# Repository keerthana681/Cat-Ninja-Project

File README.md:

# Cat Ninja Handheld Console Game
 
A handheld gaming console built from scratch for UT Austin's ECE319H (Introduction to Embedded Systems), featuring a custom PCB, dual-LCD displays, and an interrupt-driven game engine.
 
## Overview
 
Cat Ninja is a fully custom embedded gaming handheld built around the TI MSPM0 microcontroller. The project spans the full hardware-software stack: a custom-designed PCB, analog input sampling via joystick and slide potentiometer, a discrete DAC for in-game sound, and a real-time game engine driven by hardware timers and interrupts.
 
## Features
 
- **Custom PCB** designed in KiCad, integrating the TI MSPM0 microcontroller with dual-LCD displays and a joystick interface
- **Dual-LCD setup** — one screen renders the live game, the other displays the score and a reactive cat sprite (happy when fish are sliced, sad when a bomb is hit or a life is lost)
- **Original hand-drawn sprite art** for the cat cursor, fish, sliced-fish states, and bombs
- **Analog input sampling** via ADC for the joystick (menu navigation and cursor movement) and slide potentiometer (in-game volume control)
- **5-bit binary-weighted DAC** for real-time sound effects (slicing, explosions, and more)
- **Interrupt-driven game engine** written in C++, using SysTick and TimerG12 for periodic game logic, rendering, and input polling
- **Finite state machine (FSM) architecture** driving the title menu, settings, gameplay, pause, and game-over screens
## How to Play
 
**Menu Navigation**
- On the title screen, move the joystick to switch between **Info**, **Settings**, and **Play**
- One button **selects** the highlighted option; the other button **goes back** to the previous screen
- **Info** explains how to play
- **Settings** lets you change the display language (English/Spanish)
**Gameplay**
- Move the cat paw cursor around the screen using the joystick
- Press the select button to **slice** — this triggers a slicing sound and swaps the fish sprite to its sliced state
- Fish rise and fall across the screen at random; slice them to score points
- Bombs appear at random alongside the fish — avoid slicing these
- You have **3 lives**. You lose a life if you let a fish fall unsliced, or if you slice a bomb (which also triggers an explosion sound)
- When you run out of lives, the game ends with a crying-cat sound effect
- The volume of in-game sound effects is controlled in real time by the slide potentiometer
## Hardware
 
- TI MSPM0 microcontroller
- Dual-LCD display setup
- Joystick + slide potentiometer analog inputs
- Custom binary-weighted DAC circuit for audio output
- PCB designed and fabricated for this project (see `/hardware` for KiCad files and schematics)
## Software
 
- Core game engine written in C++
- SysTick and TimerG12 used for periodic, interrupt-driven task scheduling
- ADC driver for analog input sampling
- DAC output driver for sound playback
## Team
 
Built by Keerthana Mangalpally and Kaitlyn Chen for ECE319H at UT Austin.
 
## Acknowledgments & License
 
This project uses hardware driver code adapted from course materials provided by Dr. Jonathan Valvano for UT Austin's embedded systems curriculum, used under the license below.
 
```
Simplified BSD License (FreeBSD License)
Copyright © 2025, Jonathan Valvano, All rights reserved.
 
Redistribution and use in source and binary forms, with or without modification,
are permitted provided that the following conditions are met:
 
1. Redistributions of source code must retain the above copyright notice,
   this list of conditions and the following disclaimer.
2. Redistributions in binary form must reproduce the above copyright notice,
   this list of conditions and the following disclaimer in the documentation
   and/or other materials provided with the distribution.
 
THIS SOFTWARE IS PROVIDED BY THE COPYRIGHT HOLDERS AND CONTRIBUTORS "AS IS"
AND ANY EXPRESS OR IMPLIED WARRANTIES, INCLUDING, BUT NOT LIMITED TO, THE
IMPLIED WARRANTIES OF MERCHANTABILITY AND FITNESS FOR A PARTICULAR PURPOSE
ARE DISCLAIMED. IN NO EVENT SHALL THE COPYRIGHT OWNER OR CONTRIBUTORS BE
LIABLE FOR ANY DIRECT, INDIRECT, INCIDENTAL, SPECIAL, EXEMPLARY, OR CONSEQUENTIAL
DAMAGES (INCLUDING, BUT NOT LIMITED TO, PROCUREMENT OF SUBSTITUTE GOODS OR SERVICES;
LOSS OF USE, DATA, OR PROFITS; OR BUSINESS INTERRUPTION) HOWEVER CAUSED
AND ON ANY THEORY OF LIABILITY, WHETHER IN CONTRACT, STRICT LIABILITY,
OR TORT (INCLUDING NEGLIGENCE OR OTHERWISE) ARISING IN ANY WAY OUT OF THE
USE OF THIS SOFTWARE, EVEN IF ADVISED OF THE POSSIBILITY OF SUCH DAMAGE.
 
The views and conclusions contained in the software and documentation are
those of the authors and should not be interpreted as representing official
policies, either expressed or implied, of the FreeBSD Project.
```
 
For more information on the original course materials, see [Dr. Valvano's course page](http://users.ece.utexas.edu/~valvano/).

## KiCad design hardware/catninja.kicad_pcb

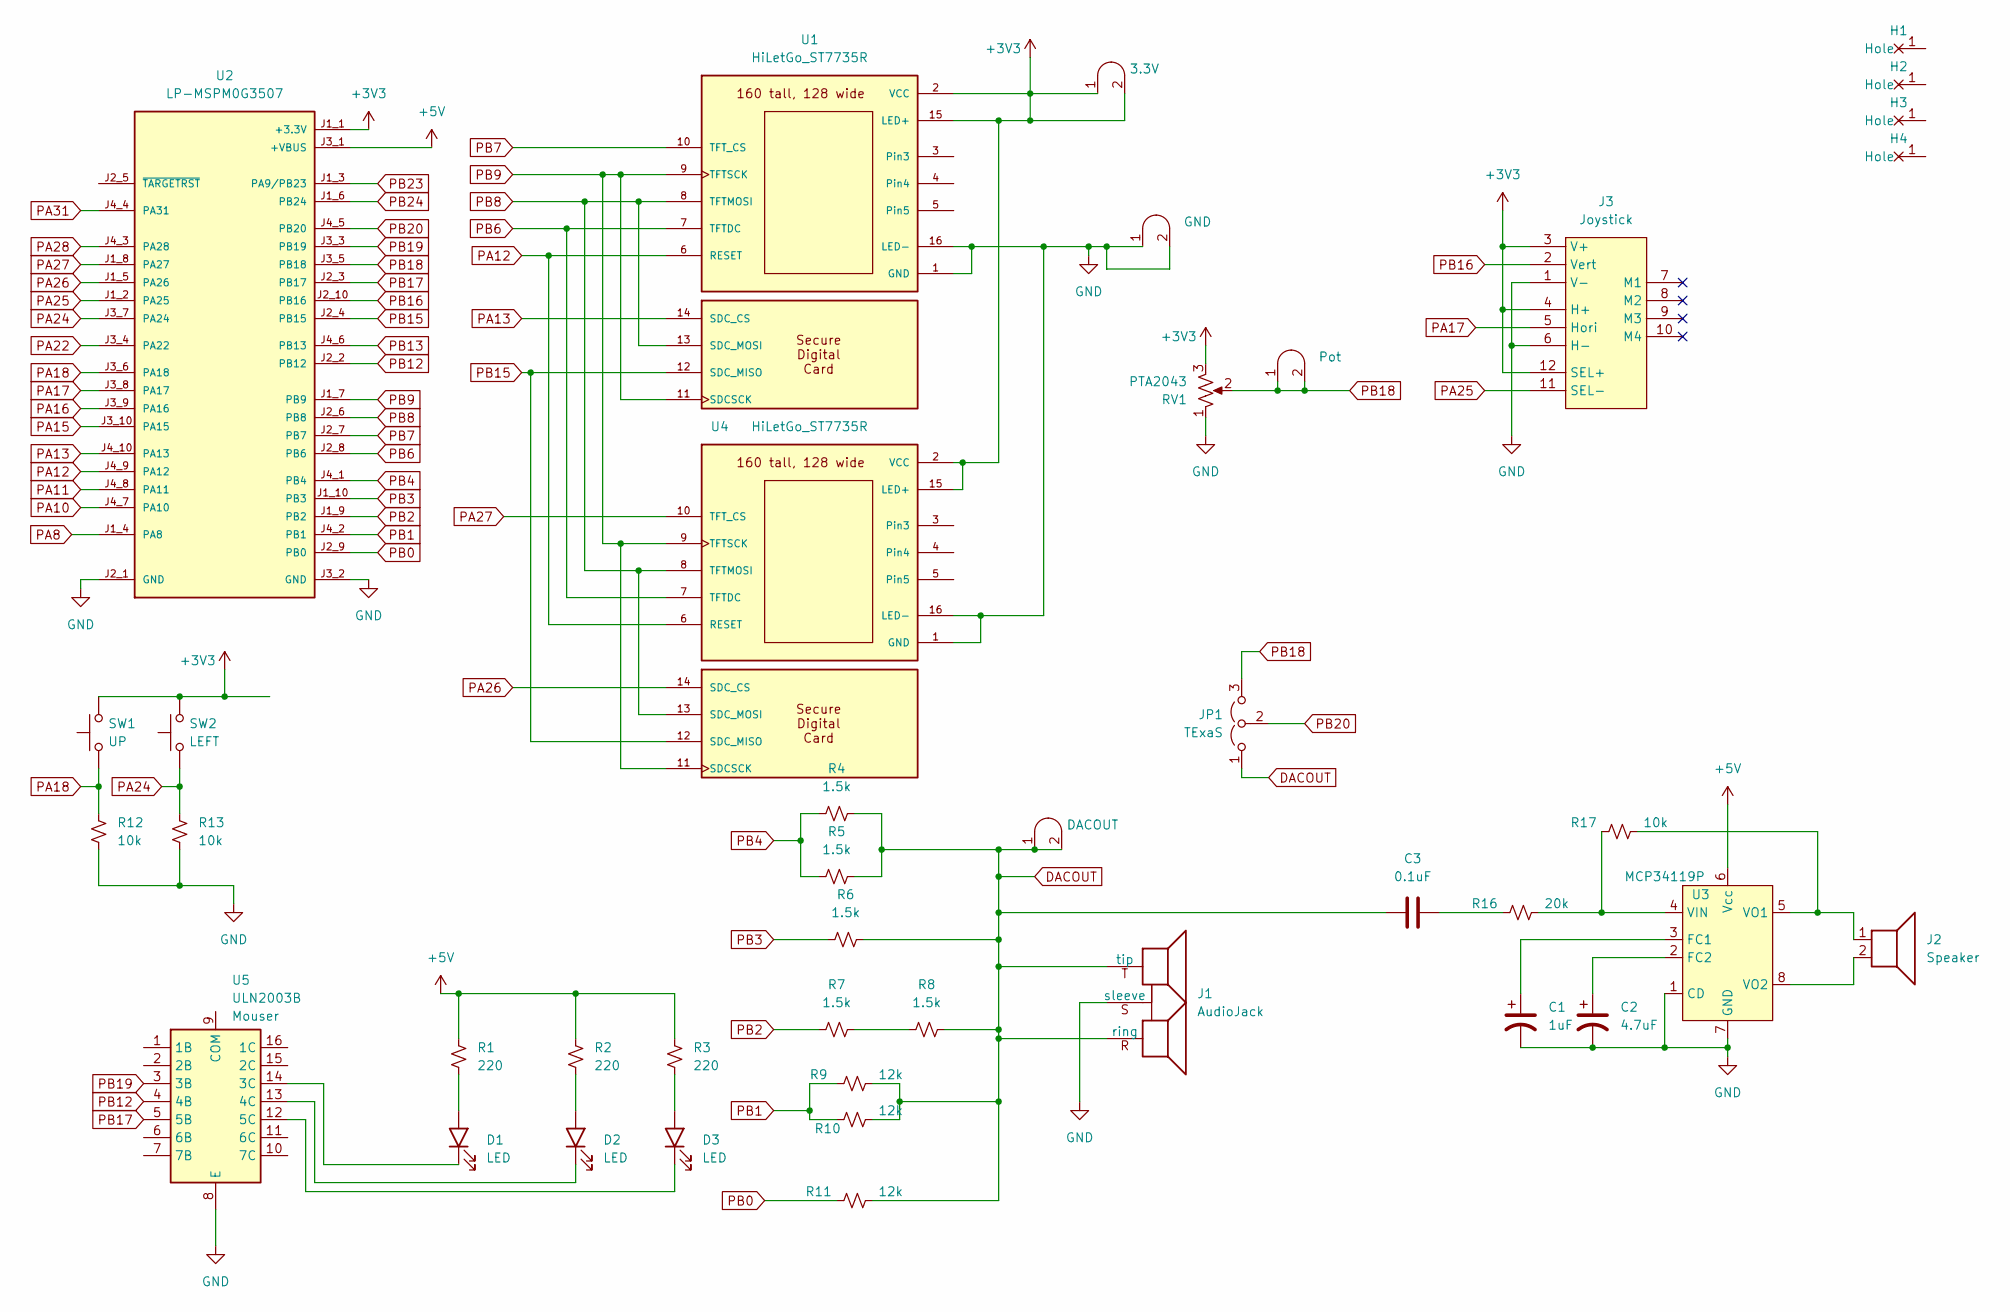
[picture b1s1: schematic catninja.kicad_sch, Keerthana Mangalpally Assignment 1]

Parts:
C1: 1uF; CP_Radial_Tantal200mil
C2: 4.7uF; CP_Radial_Tantal200mil
C3: 0.1uF; C_Axial_200mil
D1, D2, D3: LED; LED_D5.0mm
H1, H2, H3, H4: MountingHole_4_40
J1: AudioJack; Jack_3.5mm_CUI_SJ1-3523N_Horizontal
J2: Speaker; PinHeader_1x02_P2.54mm_Vertical
J3: Joystick; SparkfunJoystick
J4: Pot; Testpoint_1x02_P2.54mm
J6: GND; Testpoint_1x02_P2.54mm
J7: DACOUT; Testpoint_1x02_P2.54mm
JP1: TExaS; PinHeader_1x03_P2.54mm_Vertical
R1, R2, R3: 220; R_Axial_DIN0204_L3.6mm_D1.6mm_P7.62mm_Horizontal
R4, R5, R6, R7, R8: 1.5k; R_Axial_DIN0204_L3.6mm_D1.6mm_P7.62mm_Horizontal
R9, R10, R11: 12k; R_Axial_DIN0204_L3.6mm_D1.6mm_P7.62mm_Horizontal
R12, R13, R17: 10k; R_Axial_DIN0204_L3.6mm_D1.6mm_P7.62mm_Horizontal
R16: 20k; R_Axial_DIN0204_L3.6mm_D1.6mm_P7.62mm_Horizontal
RV1: PTA2043; PTA2043pot
SW1: UP; SW_PUSH_6mm
SW2: LEFT; SW_PUSH_6mm
TP1: 3.3V; Testpoint_1x02_P2.54mm
U1, U4: HiLetGo_ST7735R; hiletgo_st7735r
U2: LP-MSPM0G3507; ti_LP_MSPM0G3507
U3: MCP34119P; DIP-8_W7.62mm_LongPads
U5: ULN2003B; DIP-16_W7.62mm

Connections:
+3V3: J3.3 (V+), J3.4 (H+), J3.12 (SEL+), RV1.3, SW1.2, SW2.2, TP1.1 (A), TP1.2 (B), U1.2 (VCC), U1.15 (LED+), U2.J1_1 (+3.3V), U4.2 (VCC), U4.15 (LED+)
+5V: R1.1, R2.1, R3.1, U2.J3_1 (+VBUS), U3.6 (Vcc)
DACOUT: C3.1, J1.R (ring), J1.T (tip), J7.1 (A), J7.2 (B), JP1.1 (A), R4.1, R5.1, R6.1, R8.1, R9.1, R10.1, R11.1
GND: C1.2, C2.2, J1.S (sleeve), J3.1 (V-), J3.6 (H-), J6.1 (A), J6.2 (B), R12.2, R13.2, RV1.1, U1.1 (GND), U1.16 (LED-), U2.J2_1 (GND), U2.J3_2 (GND), U3.1 (CD), U3.7 (GND), U4.1 (GND), U4.16 (LED-), U5.8 (E)
unnamed: C3.2, R16.2
unnamed: D1.2 (A), R1.2
unnamed: D1.1 (K), U5.14 (3C)
unnamed: D2.2 (A), R2.2
unnamed: D2.1 (K), U5.13 (4C)
unnamed: D3.2 (A), R3.2
unnamed: D3.1 (K), U5.12 (5C)
unnamed: R7.1, R8.2
unnamed: C1.1, U3.3 (FC1)
unnamed: C2.1, U3.2 (FC2)
unnamed: R16.1, R17.2, U3.4 (VIN)
unnamed: J2.1, R17.1, U3.5 (VO1)
unnamed: J2.2, U3.8 (VO2)
PA8: U2.J1_4 (PA8)
PA10: U2.J4_7 (PA10)
PA11: U2.J4_8 (PA11)
PA12: U1.6 (RESET), U2.J4_9 (PA12), U4.6 (RESET)
PA13: U1.14 (SDC_CS), U2.J4_10 (PA13)
PA15: U2.J3_10 (PA15)
PA16: U2.J3_9 (PA16)
PA17: J3.5 (Hori), U2.J3_8 (PA17)
PA18: R12.1, SW1.1, U2.J3_6 (PA18)
PA22: U2.J3_4 (PA22)
PA24: R13.1, SW2.1, U2.J3_7 (PA24)
PA25: J3.11 (SEL-), U2.J1_2 (PA25)
PA26: U2.J1_5 (PA26), U4.14 (SDC_CS)
PA27: U2.J1_8 (PA27), U4.10 (TFT_CS)
PA28: U2.J4_3 (PA28)
PA31: U2.J4_4 (PA31)
PB0: R11.2, U2.J2_9 (PB0)
PB1: R9.2, R10.2, U2.J4_2 (PB1)
PB2: R7.2, U2.J1_9 (PB2)
PB3: R6.2, U2.J1_10 (PB3)
PB4: R4.2, R5.2, U2.J4_1 (PB4)
PB6: U1.7 (TFTDC), U2.J2_8 (PB6), U4.7 (TFTDC)
PB7: U1.10 (TFT_CS), U2.J2_7 (PB7)
PB8: U1.8 (TFTMOSI), U1.13 (SDC_MOSI), U2.J2_6 (PB8), U4.8 (TFTMOSI), U4.13 (SDC_MOSI)
PB9: U1.9 (TFTSCK), U1.11 (SDCSCK), U2.J1_7 (PB9), U4.9 (TFTSCK), U4.11 (SDCSCK)
PB12: U2.J2_2 (PB12), U5.4 (4B)
PB13: U2.J4_6 (PB13)
PB15: U1.12 (SDC_MISO), U2.J2_4 (PB15), U4.12 (SDC_MISO)
PB16: J3.2 (Vert), U2.J2_10 (PB16)
PB17: U2.J2_3 (PB17), U5.5 (5B)
PB18: J4.1 (A), J4.2 (B), JP1.3 (B), RV1.2, U2.J3_5 (PB18)
PB19: U2.J3_3 (PB19), U5.3 (3B)
PB20: JP1.2 (C), U2.J4_5 (PB20)
PB23: U2.J1_3 (PA9/PB23)
PB24: U2.J1_6 (PB24)

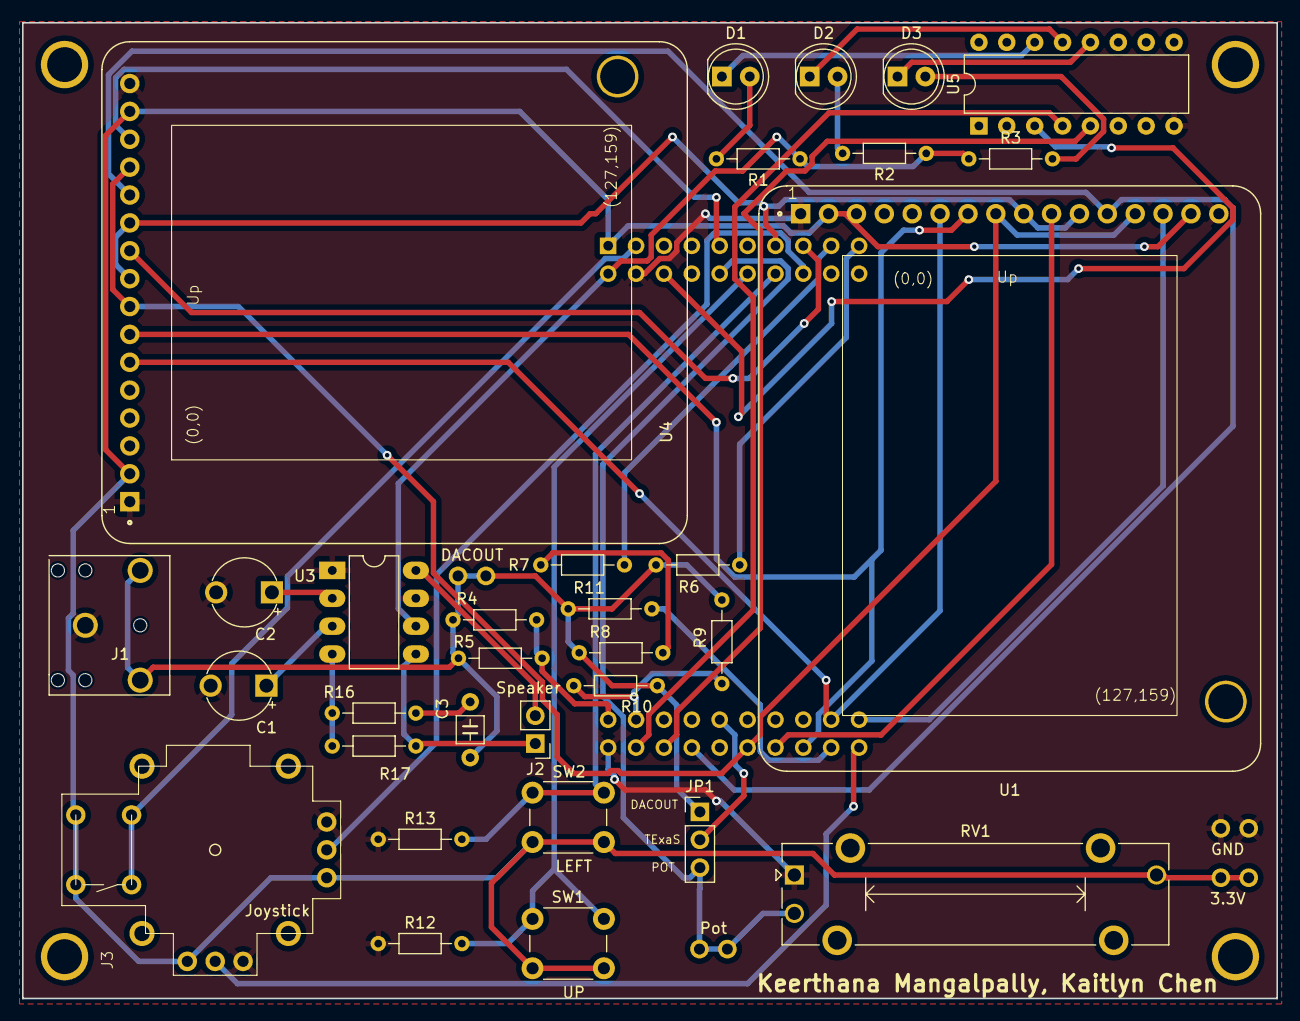
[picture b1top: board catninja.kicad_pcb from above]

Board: 2 copper layers, 114.3 x 88.9 mm, 41 parts (1 on the bottom side), 41 nets.

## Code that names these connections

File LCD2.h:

// LCD2.h
// Driver for the second ST7735 display (portrait orientation, 128x160).
// Shares SPI1 (PB8=MOSI, PB9=SCLK, PA13=DC, PB15=RESET) with LCD1.
// LCD1 chip-select stays on PB6, LCD2 chip-select is PA26 (PINCM index 58), active-low.
// LCD2 is vertical — used for score, lives, and reaction faces.
//
// Kaitlyn Chen and Keerthana Mangalpally
// ECE319H Lab 9, Spring 2026

#ifndef LCD2_H
#define LCD2_H
#include <stdint.h>

// ── Color constants (16-bit RGB565, same encoding as ST7735) ─────────────
#define LCD2_BLACK    0x0000
#define LCD2_WHITE    0xFFFF
#define LCD2_RED      0x001F
#define LCD2_GREEN    0x07E0
#define LCD2_BLUE     0xF800
#define LCD2_CYAN     0xFFE0
#define LCD2_YELLOW   0x07FF
#define LCD2_MAGENTA  0xF81F
#define LCD2_ORANGE   0x041F
#define LCD2_DARKGREY 0x39E7

// ── LCD2 display dimensions (portrait mode) ───────────────────────────────
#define LCD2_WIDTH   128
#define LCD2_HEIGHT  160

// ── Public API ────────────────────────────────────────────────────────────

// Initialize LCD2 hardware (PA26 GPIO + ST7735 init sequence, portrait mode).
// Must be called AFTER ST7735_InitR/InitPrintf (which sets up SPI1).
void LCD2_Init(void);

// Fill the entire display with a solid color.
void LCD2_FillScreen(uint16_t color);

// Display the current score as large 7-segment-style digits.
// score: 0 to 9999 (values >= 1000 show 4 digits).
void LCD2_ShowScore(uint32_t score);

// Display lives remaining as colored indicator squares (3 squares max).
// lives: 0-3 (0 = all grey, 3 = all red).
void LCD2_ShowLives(uint8_t lives);

// Draw a cartoon reaction face matching the current FSM game state.
// state: pass S_TITLE, S_GAMEPLAY, S_PAUSED, or S_GAMEOVER (from game.h).
void LCD2_ShowReaction(uint8_t state);

// Display the current difficulty level (0-9) at the bottom of the portrait display.
// Call during gameplay whenever the level changes.
void LCD2_ShowLevel(uint8_t level);

#endif // LCD2_H

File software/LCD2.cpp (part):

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// Second ST7735 display driver — portrait mode (128×160 pixels).
//
// Hardware wiring:
//   PA26 (PINCM 58) — LCD2 chip-select (active-low)
//   PB6             — DC (shared with LCD1; command=low, data=high)
//   PB8             — SPI1 MOSI (shared)
//   PB9             — SPI1 SCLK (shared)
//   PA12            — Hardware reset (shared; LCD1 init already pulses this)
//
// SPI1 is initialized by LCD1's SPI_Init() call inside ST7735_InitR().
// LCD2_Init() only configures PA26 as a GPIO output, then sends the ST7735
// command sequence to LCD2 via its own chip-select.  The two displays are
// completely independent in software: only the CS line distinguishes them.
//
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#include "../inc/SPI.h"

// ── Pin definitions ───────────────────────────────────────────────────────
#define LCD2_CS_PINCM  59         // PINCM index for PA27
#define LCD2_CS_BIT    (1UL<<27)  // PA27 bitmask

// ── ST7735 command bytes ──────────────────────────────────────────────────
#define ST7735_SWRESET  0x01
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#define LCD2_MADCTL_PORTRAIT  0xC0

// ── Low-level SPI helpers ─────────────────────────────────────────────────
// Each function asserts PA26 (LCD2_CS), uses PB6 (DC) shared with LCD1,
// then deasserts PA26.  LCD1 (PA27) remains deasserted throughout, so it
// ignores all traffic here.

static void LCD2_Cmd(uint8_t cmd){
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// ── Initialization ────────────────────────────────────────────────────────

void LCD2_Init(void){
    // Configure PA26 as GPIO output, idle-high (CS deasserted)
    // IOMUX->SECCFG.PINCM[LCD2_CS_PINCM] = 0x00000081;  // GPIO function, output
    // GPIOA->DOE31_0    |= LCD2_CS_BIT;
    // GPIOA->DOUTSET31_0 = LCD2_CS_BIT;   // CS = 1 (idle)
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
    // ── ST7735R init sequence (BLACKTAB, portrait) ────────────────────────
    // Mirrors the Rcmd1 + Rcmd2red + Rcmd3 sequences from ST7735.cpp,
    // but uses LCD2_Cmd/LCD2_Data so PA26 is asserted instead of PA27.

    // Software reset
    LCD2_Cmd(ST7735_SWRESET); Clock_Delay1ms(150);
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
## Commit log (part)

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2026-04-22 Add initial project files
2026-04-22 fixed sound output interactions + slidepot
2026-04-22 added cat sprites on lcd2 and updated sounds
2026-04-22 made game aesthetics better
2026-04-23 remove old dead code
